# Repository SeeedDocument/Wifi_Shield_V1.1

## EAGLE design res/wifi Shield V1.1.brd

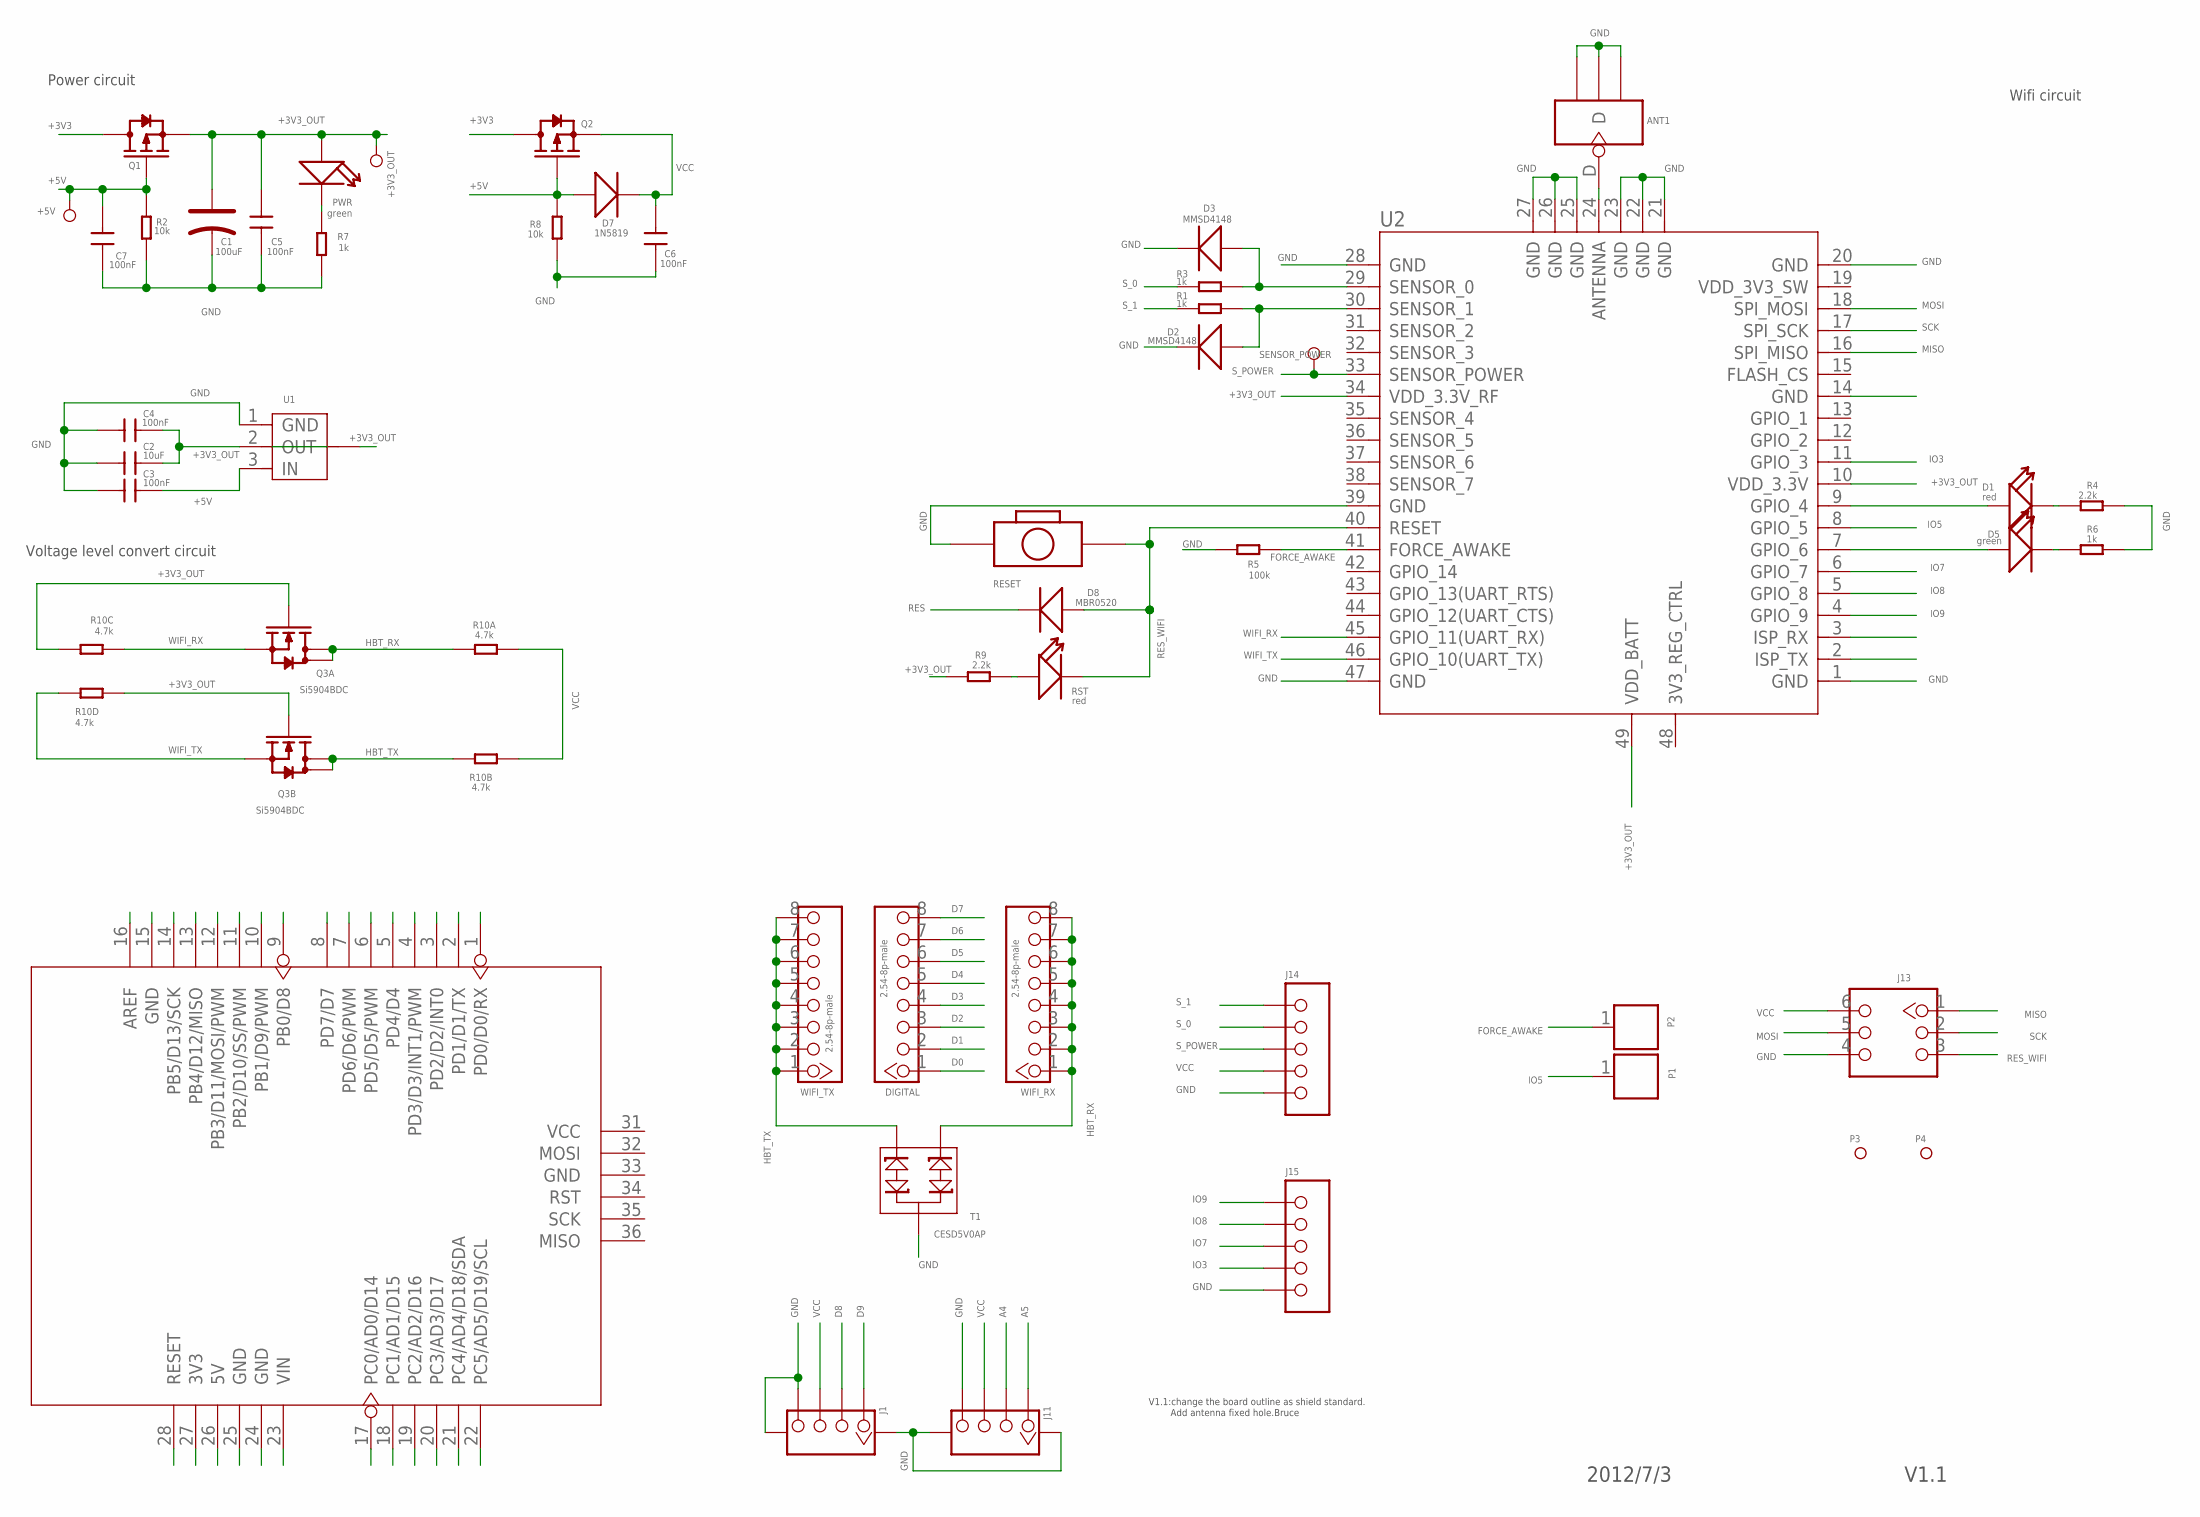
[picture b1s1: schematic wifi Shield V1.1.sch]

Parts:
+3V3_OUT, +5V: PAD-TEST-POINT-CIRCLE_SIZE_3030; TP_3535
ANT1: ANTENNA-U-FL; 4P-U-FL
C1: 100uF; AVX-B
C2: 10uF; 0603
C3, C4, C5, C6, C7: 100nF; 0603
D1: red; LED-0603
D2, D3: MMSD4148; SOD123-2.7X1.6
D5: green; LED-0603
D7: 1N5819; D2010
D8: MBR0520; SOD123-2.7X1.6
DIGITAL: 2.54-8p-male; 8P-2.54
J1, J11: TWIG-4P-2.0-SMD-FEMALE-REINFORCE'90D'; 4P-SMD-2.0-90D
J13: HEADER-2X3P-2.54; 2X3P-2.54
J14, J15: HEADER-5P-2.54; 5P-2.54
P1, P2: PAD'60/30'; 1P-65/35MIL
P3, P4: PAD-MARK; ROUND-MARK-1.0
PWR: green; LED-0603
Q1, Q2: MOSFET-P'SI2323CDS/SI2305DS<BR>'; SOT23
Q3: Si5904BDC; 1206-8
R1, R3, R6, R7: 1k; 0603
R2, R8: 10k; 0603
R4, R9: 2.2k; 0603
R5: 100k; 0603
R10: 4.7k; R1206-8
RESET: BOTTON-2P-90; 2P-7.62X3.56-90D
RST: red; LED-0603
SENSOR_POWER: PAD-TEST-POINT-CIRCLE_SIZE_3030; TP_3535
T1: CESD5V0AP; SOT23
U1: LD1117SOT89; SOT89
U2: WIFI-RN-171; 49P-1.27-26.67X17.78
U4: ARDUINO
WIFI_RX: 2.54-8p-male; 8P-2.54
WIFI_TX: 2.54-8p-male; 8P-2.54

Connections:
+3V3: Q1.3 (D), Q2.3 (D), U4.27 (3V3)
+3V3_OUT: +3V3_OUT.T, C1.+, C2.2, C4.2, C5.1, PWR.+, Q1.2 (S), Q3.2 (G), Q3.4 (G), R9.2, R10.5 (2), R10.6 (2), U1.2 (OUT), U1.4 (TAB), U2.10 (VDD_3.3V), U2.34 (VDD_3.3V_RF), U2.49 (VDD_BATT)
+5V: +5V.T, C3.2, C7.1, D7.+, Q1.1 (G), Q2.1 (G), R2.1, R8.1, U1.3 (IN), U4.26 (5V)
A0: U4.17 (PC0/AD0/D14)
A1: U4.18 (PC1/AD1/D15)
A2: U4.19 (PC2/AD2/D16)
A3: U4.20 (PC3/AD3/D17)
A4: J11.2, U4.21 (PC4/AD4/D18/SDA)
A5: J11.1, U4.22 (PC5/AD5/D19/SCL)
AREF: U4.16 (AREF)
D0: DIGITAL.1, U4.1 (PD0/D0/RX)
D1: DIGITAL.2, U4.2 (PD1/D1/TX)
D2: DIGITAL.3, U4.3 (PD2/D2/INT0)
D3: DIGITAL.4, U4.4 (PD3/D3/INT1/PWM)
D4: DIGITAL.5, U4.5 (PD4/D4)
D5: DIGITAL.6, U4.6 (PD5/D5/PWM)
D6: DIGITAL.7, U4.7 (PD6/D6/PWM)
D7: DIGITAL.8, U4.8 (PD7/D7)
D8: J1.2, U4.9 (PB0/D8)
D9: J1.1, U4.10 (PB1/D9/PWM)
D10: U4.11 (PB2/D10/SS/PWM)
D11: U4.12 (PB3/D11/MOSI/PWM)
D12: U4.13 (PB4/D12/MISO)
D13: U4.14 (PB5/D13/SCK)
FORCE_AWAKE: P2.1, R5.1, U2.41 (FORCE_AWAKE)
GND: ANT1.GND1, ANT1.GND2, ANT1.GND3, C1.-, C2.1, C3.1, C4.1, C5.2, C6.2, C7.2, D2.1 (-), D3.1 (-), J1.4, J1.SS1, J1.SS2, J11.4, J11.SS1, J11.SS2, J13.4, J14.5, J15.5, R2.2, R4.1, R5.2, R6.1, R7.1, R8.2, RESET.P$2 (2), T1.3, U1.1 (GND), U2.1 (GND), U2.14 (GND), U2.20 (GND), U2.21 (GND), U2.22 (GND), U2.23 (GND), U2.25 (GND), U2.26 (GND), U2.27 (GND), U2.28 (GND), U2.39 (GND), U2.47 (GND), U4.15 (GND), U4.24 (GND), U4.25 (GND)
HBT_RX: Q3.7 (D), Q3.8 (D), R10.1, T1.1, WIFI_RX.1, WIFI_RX.2, WIFI_RX.3, WIFI_RX.4, WIFI_RX.5, WIFI_RX.6, WIFI_RX.7, WIFI_RX.8
HBT_TX: Q3.5 (D), Q3.6 (D), R10.2 (1), T1.2, WIFI_TX.1, WIFI_TX.2, WIFI_TX.3, WIFI_TX.4, WIFI_TX.5, WIFI_TX.6, WIFI_TX.7, WIFI_TX.8
IO3: J15.4, U2.11 (GPIO_3)
IO5: P1.1, U2.8 (GPIO_5)
IO7: J15.3, U2.6 (GPIO_7)
IO8: J15.2, U2.5 (GPIO_8)
IO9: J15.1, U2.4 (GPIO_9)
MISO: J13.1, U2.16 (SPI_MISO)
MOSI: J13.5, U2.18 (SPI_MOSI)
unnamed: R9.1, RST.+
unnamed: D3.2 (+), R3.1, U2.29 (SENSOR_0)
unnamed: D2.2 (+), R1.1, U2.30 (SENSOR_1)
unnamed: D5.+, U2.7 (GPIO_6)
unnamed: ANT1.D, U2.24 (ANTENNA)
unnamed: D1.+, U2.9 (GPIO_4)
unnamed: D5.-, R6.2
unnamed: D1.-, R4.2
unnamed: PWR.-, R7.2
RES: D8.1 (-), U4.28 (RESET)
RES_WIFI: D8.2 (+), J13.3, RESET.P$1 (1), RST.-, U2.40 (RESET)
SCK: J13.2, U2.17 (SPI_SCK)
S_0: J14.2, R3.2
S_1: J14.1, R1.2
S_POWER: J14.3, SENSOR_POWER.T, U2.33 (SENSOR_POWER)
VCC: C6.1, D7.-, J1.3, J11.3, J13.6, J14.4, Q2.2 (S), R10.7 (2), R10.8 (2)
VIN: U4.23 (VIN)
WIFI_RX: Q3.1 (S), R10.3 (1), U2.45 (GPIO_11(UART_RX))
WIFI_TX: Q3.3 (S), R10.4 (1), U2.46 (GPIO_10(UART_TX))

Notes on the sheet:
Power circuit
Wifi circuit
Voltage level convert circuit
V1.1
2012/7/3
V1.1:change the board outline as shield standard.
Add antenna fixed hole.Bruce

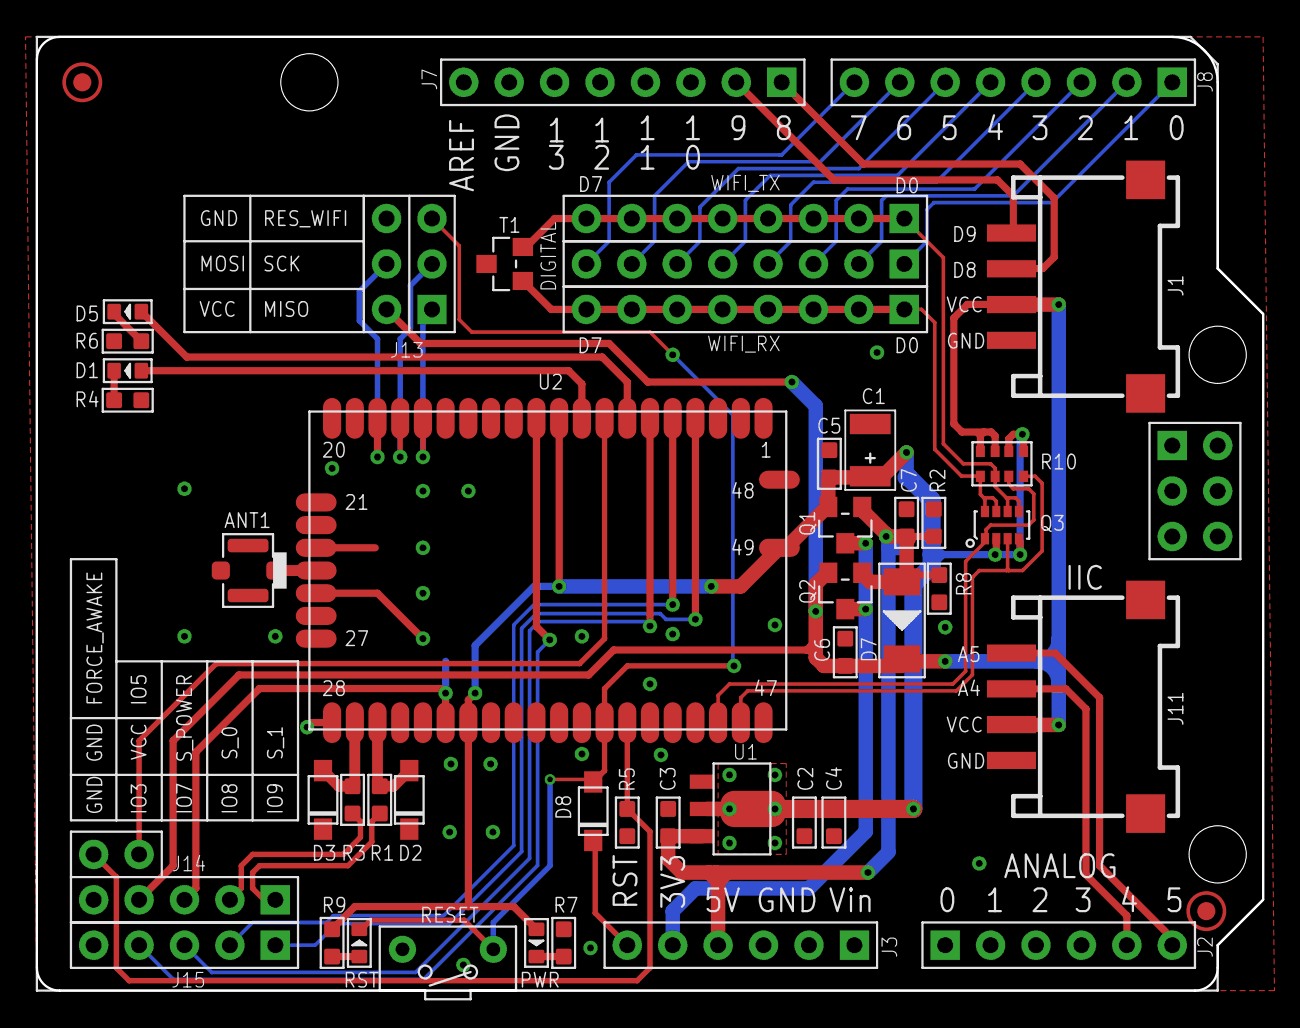
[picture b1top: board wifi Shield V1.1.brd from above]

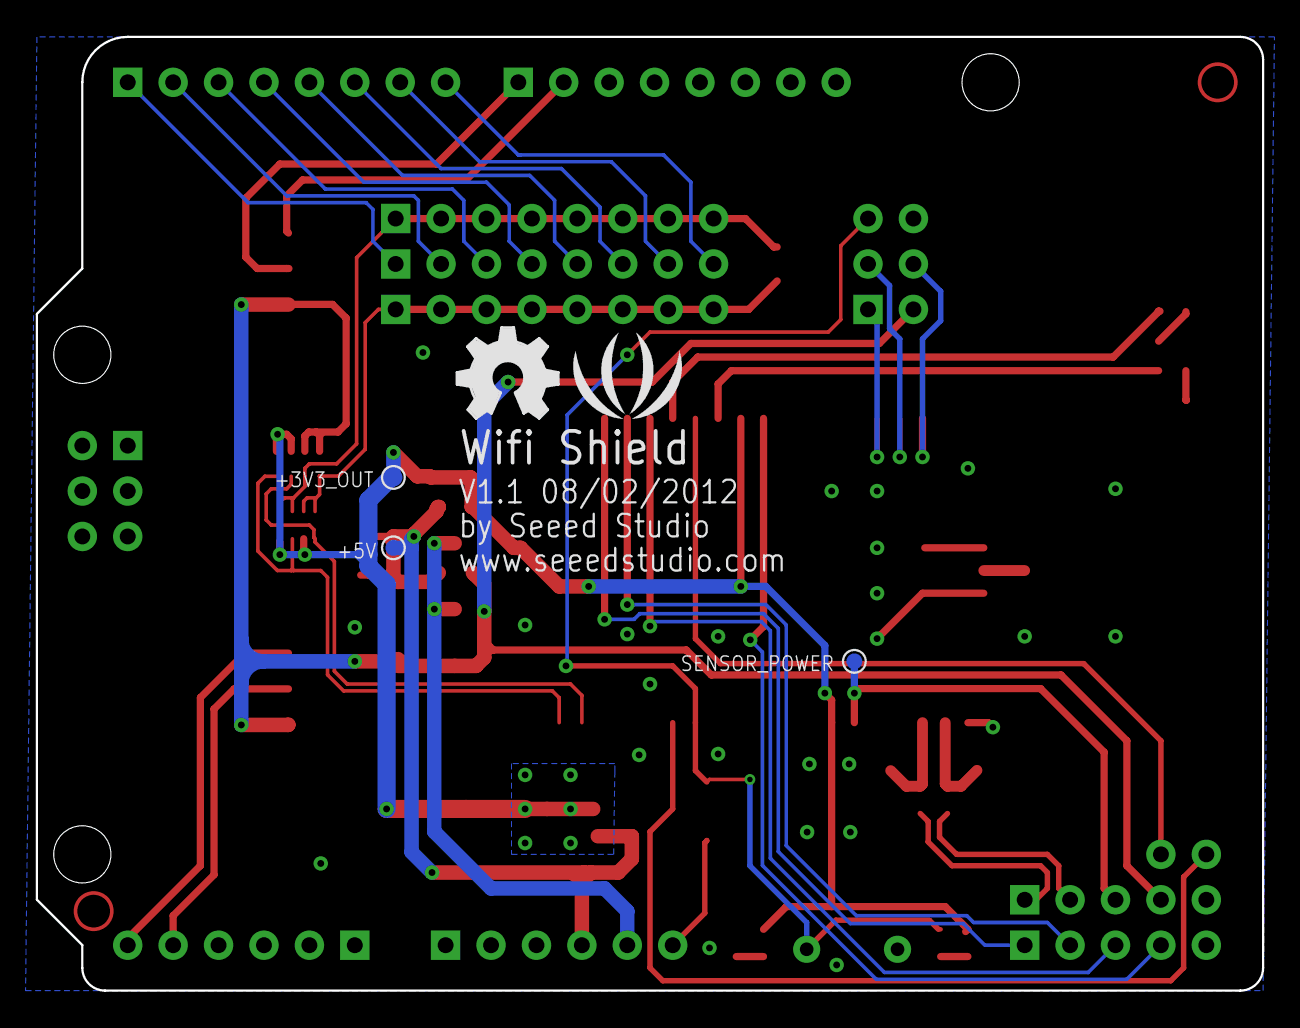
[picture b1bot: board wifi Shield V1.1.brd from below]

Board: 2 copper layers, 68.6 x 53.3 mm, 51 parts (5 on the bottom side), 44 nets.

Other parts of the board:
U$1: OSHW_FILLX200_NOTEXT
U$2: LOGO_SILK

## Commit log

2017-05-28 upgrade
2019-11-06 add
    add
